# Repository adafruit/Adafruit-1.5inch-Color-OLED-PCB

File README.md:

# PCB for the Adafruit 1.5" Color OLED display breakout board

<a href="http://www.adafruit.com/products/1431"><br/>Click here to purchase one from the Adafruit shop</a>

This is the PCB for the Adafruit 1.5" Color OLED display breakout board
Format is EagleCAD schematic and board layout

We love our black and white monochrome displays but we also like to dabble with some color now and then. Our big 1.5" color OLED displays are perfect when you need a small display with vivid, high-contrast 16-bit color. The visible portion of the OLED measures 1.5" diagonal and contains 128x128 RGB pixels, each one made of red, green and blue OLEDs. Each pixel can be set with 16-bits of resolution for a large range of colors. Because the display uses OLEDs, there is no backlight, and the contrast is very high (black is really black). We picked this display for its excellent color, this is the nicest mini OLED we could find!

This OLED uses the SSD1351 driver chip, which manages the display. You can talk to the driver chip using 4-wire write-only SPI (clock, data, chip select, data/command and an optional reset pin). Included on the fully assembled breakout is the OLED display and a small boost converter (required for providing 12V to the OLED) and a microSD card holder. This design includes built-in logic level shifting so you can use it with 3-5VDC power and logic levels. Our example code shows how to read a bitmap from the uSD card and display it all via SPI.

Of course, we wouldn't just leave you with a datasheet and a "good luck!" - [we've written a full open source graphics library that can draw pixels, lines, rectangles, circles, text and bitmaps as well as example code](https://github.com/adafruit/Adafruit-SSD1351-library). The code is written for Arduino but can be easily ported to your favorite microcontroller! We do not have a detailed wiring tutorial at this time, but if you follow the example code wiring it should work just fine.

## License

Adafruit invests time and resources providing this open source design, 
please support Adafruit and open-source hardware by purchasing 
products from Adafruit!

Designed by Adafruit Industries.  
Creative Commons Attribution, Share-Alike license, check license.txt for more information
All text above must be included in any redistribution

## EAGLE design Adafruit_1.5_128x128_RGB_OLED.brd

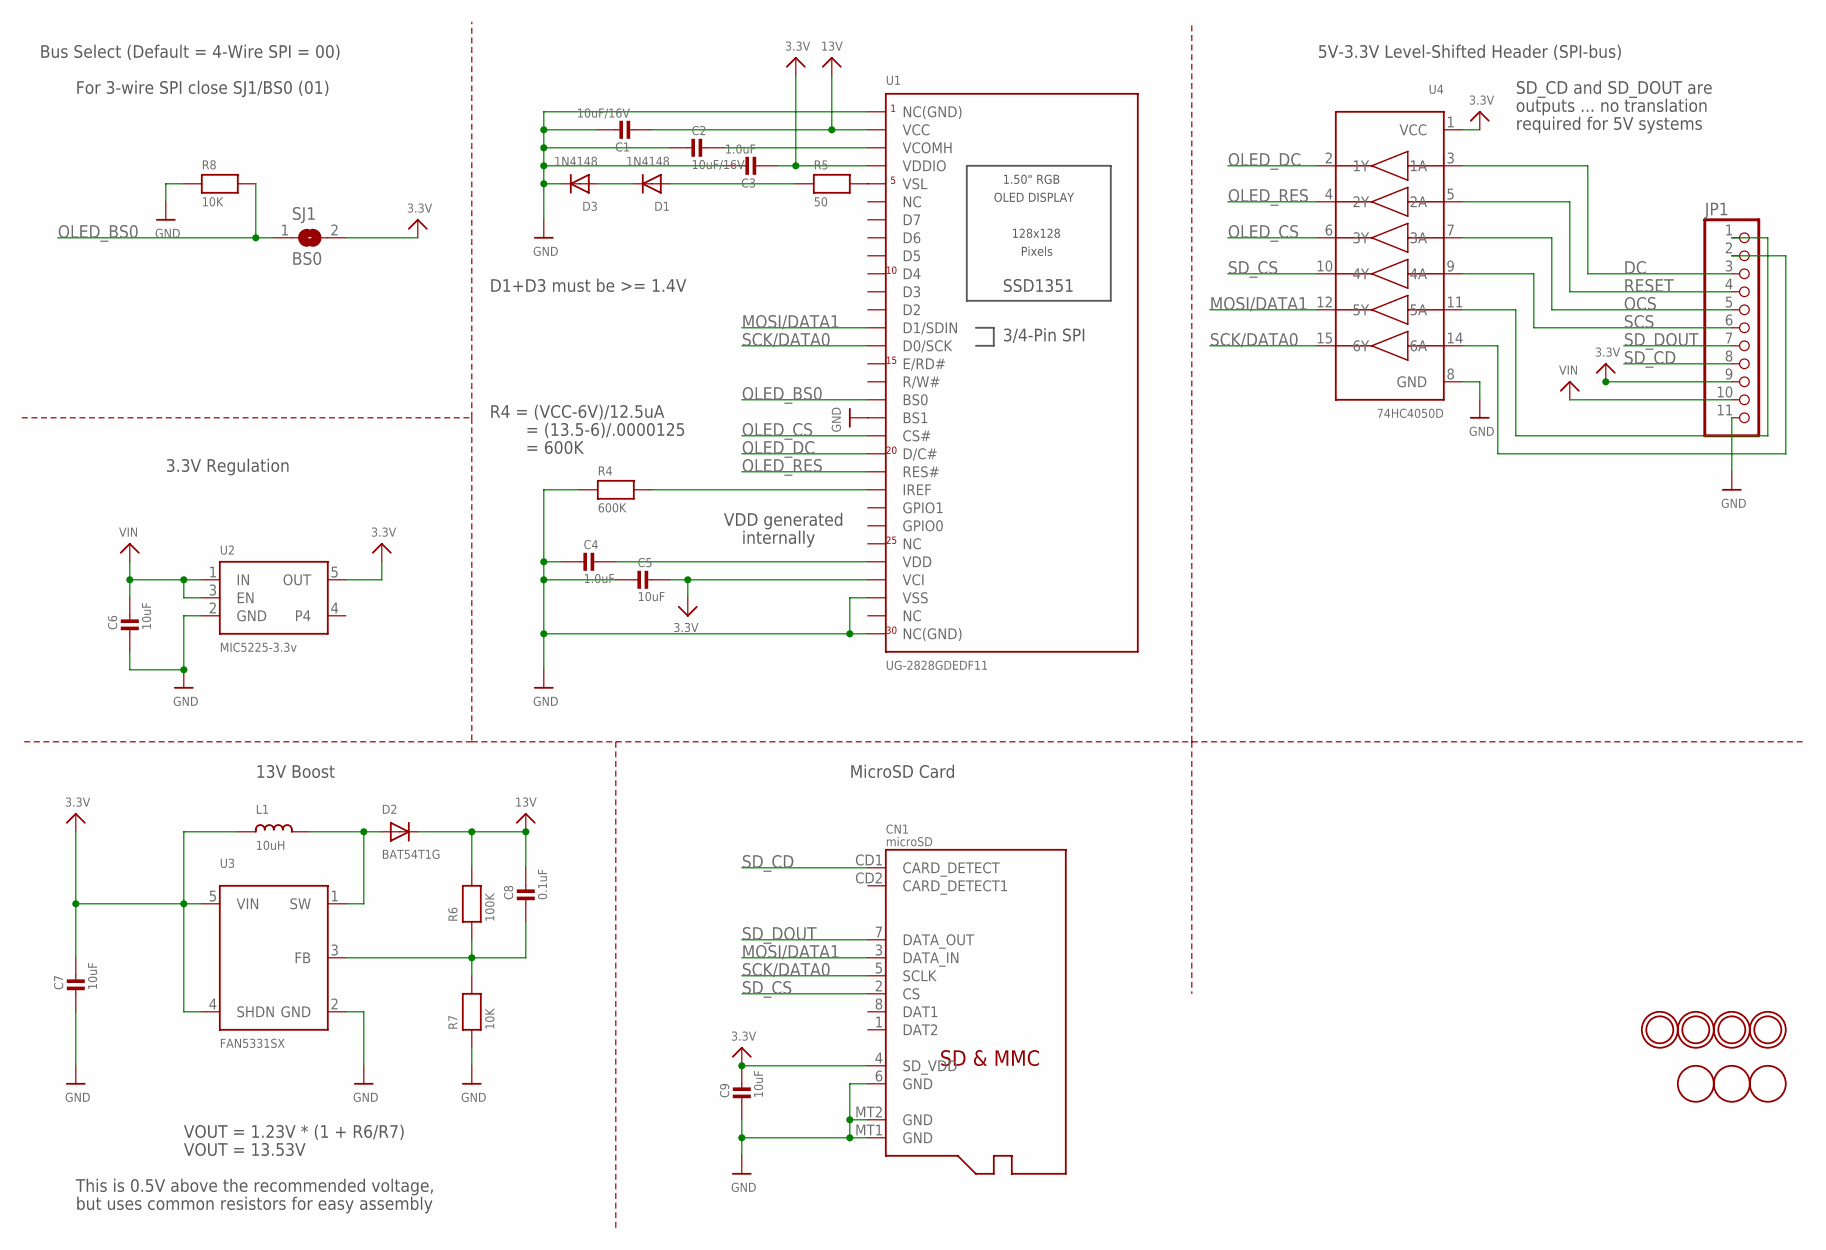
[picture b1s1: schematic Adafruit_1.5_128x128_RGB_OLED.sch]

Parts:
C1, C2: 10uF/16V; 0805
C3, C4: 1.0uF; 0805
C5, C6, C7, C9: 10uF; 0805
C8: 0.1uF; 0805
CN1: microSD; MICROSD
D1, D3: 1N4148; SOD-323
D2: BAT54T1G; SOD-123
JP1: HEADER-1X1176MIL; 1X11_ROUND_76
L1: 10uH; INDUCTOR_1007
R4: 600K; 0805
R5: 50; 0805
R6: 100K; 0805
R7, R8: 10K; 0805
SJ1: BS0; SOLDERJUMPER_REFLOW_NOPASTE
U1: UG-2828GDEDF11; FPC_XF2M-3015-1A
U2: MIC5225-3.3v; SOT23-5
U3: FAN5331SX; SOT23-5@1
U4: 74HC4050D; SOIC16
U$22, U$23, U$24, U$25: MOUNTINGHOLE2.5; MOUNTINGHOLE_2.5_PLATED
U$26, U$27, U$29: FIDUCIAL; FIDUCIAL_1MM

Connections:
3.3V: C3.2, C5.1, C7.1, C9.1, CN1.4 (SD_VDD), JP1.9, L1.P$1 (1), SJ1.2, U1.P$4 (VCI), U1.P$27 (VDDIO), U2.5 (OUT), U3.4 (SHDN), U3.5 (VIN), U4.1 (VCC)
13V: C1.2, C8.1, D2.C, R6.2, U1.P$29 (VCC)
DC: JP1.3, U4.3 (1A)
GND: C1.1, C2.2, C3.1, C4.2, C5.2, C6.2, C7.2, C9.2, CN1.6 (GND), CN1.MT1 (GND), CN1.MT2 (GND), D3.C, JP1.11, R4.1, R7.1, R8.1, U1.P$1 (NC(GND)), U1.P$3 (VSS), U1.P$13 (BS1), U1.P$30 (NC(GND)), U2.2 (GND), U3.2 (GND), U4.8 (GND)
IREF: R4.2, U1.P$9 (IREF)
MOSI/DATA1: CN1.3 (DATA_IN), U1.P$18 (D1/SDIN), U4.12 (5Y)
unnamed: C4.1, U1.P$5 (VDD)
unnamed: D2.A, L1.P$2 (2), U3.1 (SW)
unnamed: R5.2, U1.P$26 (VSL)
unnamed: D1.A, R5.1
unnamed: C8.2, R6.1, R7.2, U3.3 (FB)
unnamed: D1.C, D3.A
unnamed: JP1.1, U4.11 (5A)
unnamed: JP1.2, U4.14 (6A)
OCS: JP1.5, U4.7 (3A)
OLED_BS0: R8.2, SJ1.1, U1.P$14 (BS0)
OLED_CS: U1.P$12 (CS#), U4.6 (3Y)
OLED_DC: U1.P$11 (D/C#), U4.2 (1Y)
OLED_RES: U1.P$10 (RES#), U4.4 (2Y)
RESET: JP1.4, U4.5 (2A)
SCK/DATA0: CN1.5 (SCLK), U1.P$17 (D0/SCK), U4.15 (6Y)
SCS: JP1.6, U4.9 (4A)
SD_CD: CN1.CD1 (CARD_DETECT), JP1.8
SD_CS: CN1.2 (CS), U4.10 (4Y)
SD_DOUT: CN1.7 (DATA_OUT), JP1.7
VCOMH: C2.1, U1.P$28 (VCOMH)
VIN: C6.1, JP1.10, U2.1 (IN), U2.3 (EN)

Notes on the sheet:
Bus Select (Default = 4-Wire SPI = 00)
3.3V Regulation
VOUT = 1.23V * (1 + R6/R7)
VOUT = 13.53V
This is 0.5V above the recommended voltage,
but uses common resistors for easy assembly
13V Boost
MicroSD Card
For 3-wire SPI close SJ1/BS0 (01)
5V-3.3V Level-Shifted Header (SPI-bus)
SD_CD and SD_DOUT are
outputs ... no translation
required for 5V systems
R4 = (VCC-6V)/12.5uA
= (13.5-6)/.0000125
= 600K
D1+D3 must be >= 1.4V
VDD generated
internally

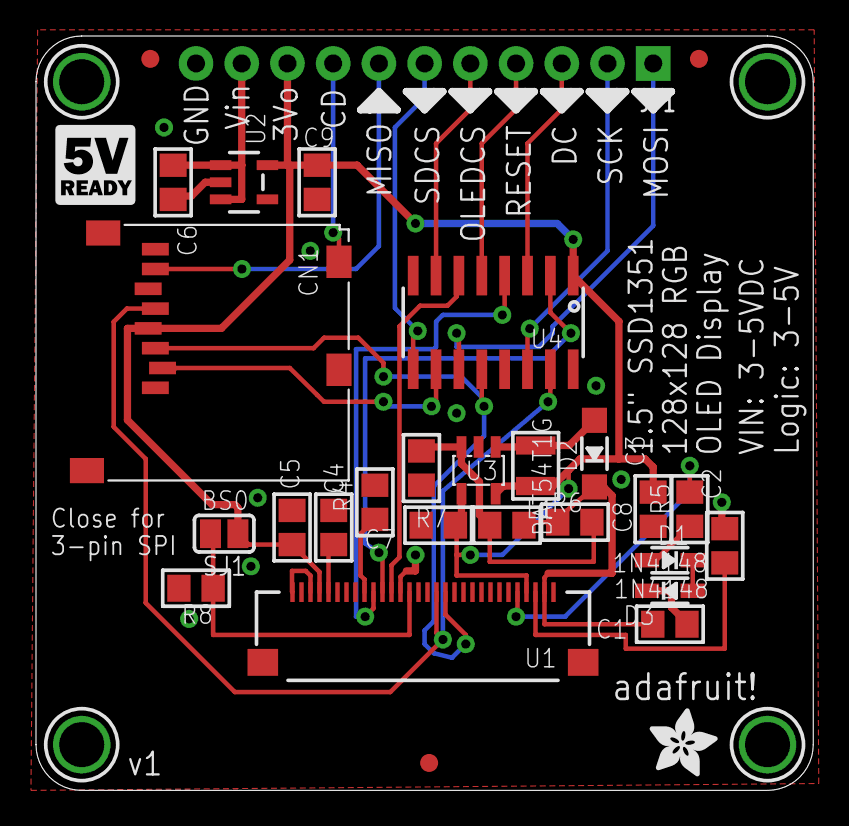
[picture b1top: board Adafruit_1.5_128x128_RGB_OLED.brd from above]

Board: 2 copper layers, 43.2 x 41.9 mm, 34 parts (0 on the bottom side), 27 nets.

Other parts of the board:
U$28: ADAFRUIT_3.5MM
U$30: LOGIC_5VREADY_5MM

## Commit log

2013-07-29 whee!
2013-07-29 read
2019-04-25 readme + image
